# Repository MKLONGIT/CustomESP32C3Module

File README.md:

# CustomESP32C3Module
This is a barebones KiCAD project featuring a fully custom built ESP32 C3 board, alongside a DIY PCB antenna made with matlab.

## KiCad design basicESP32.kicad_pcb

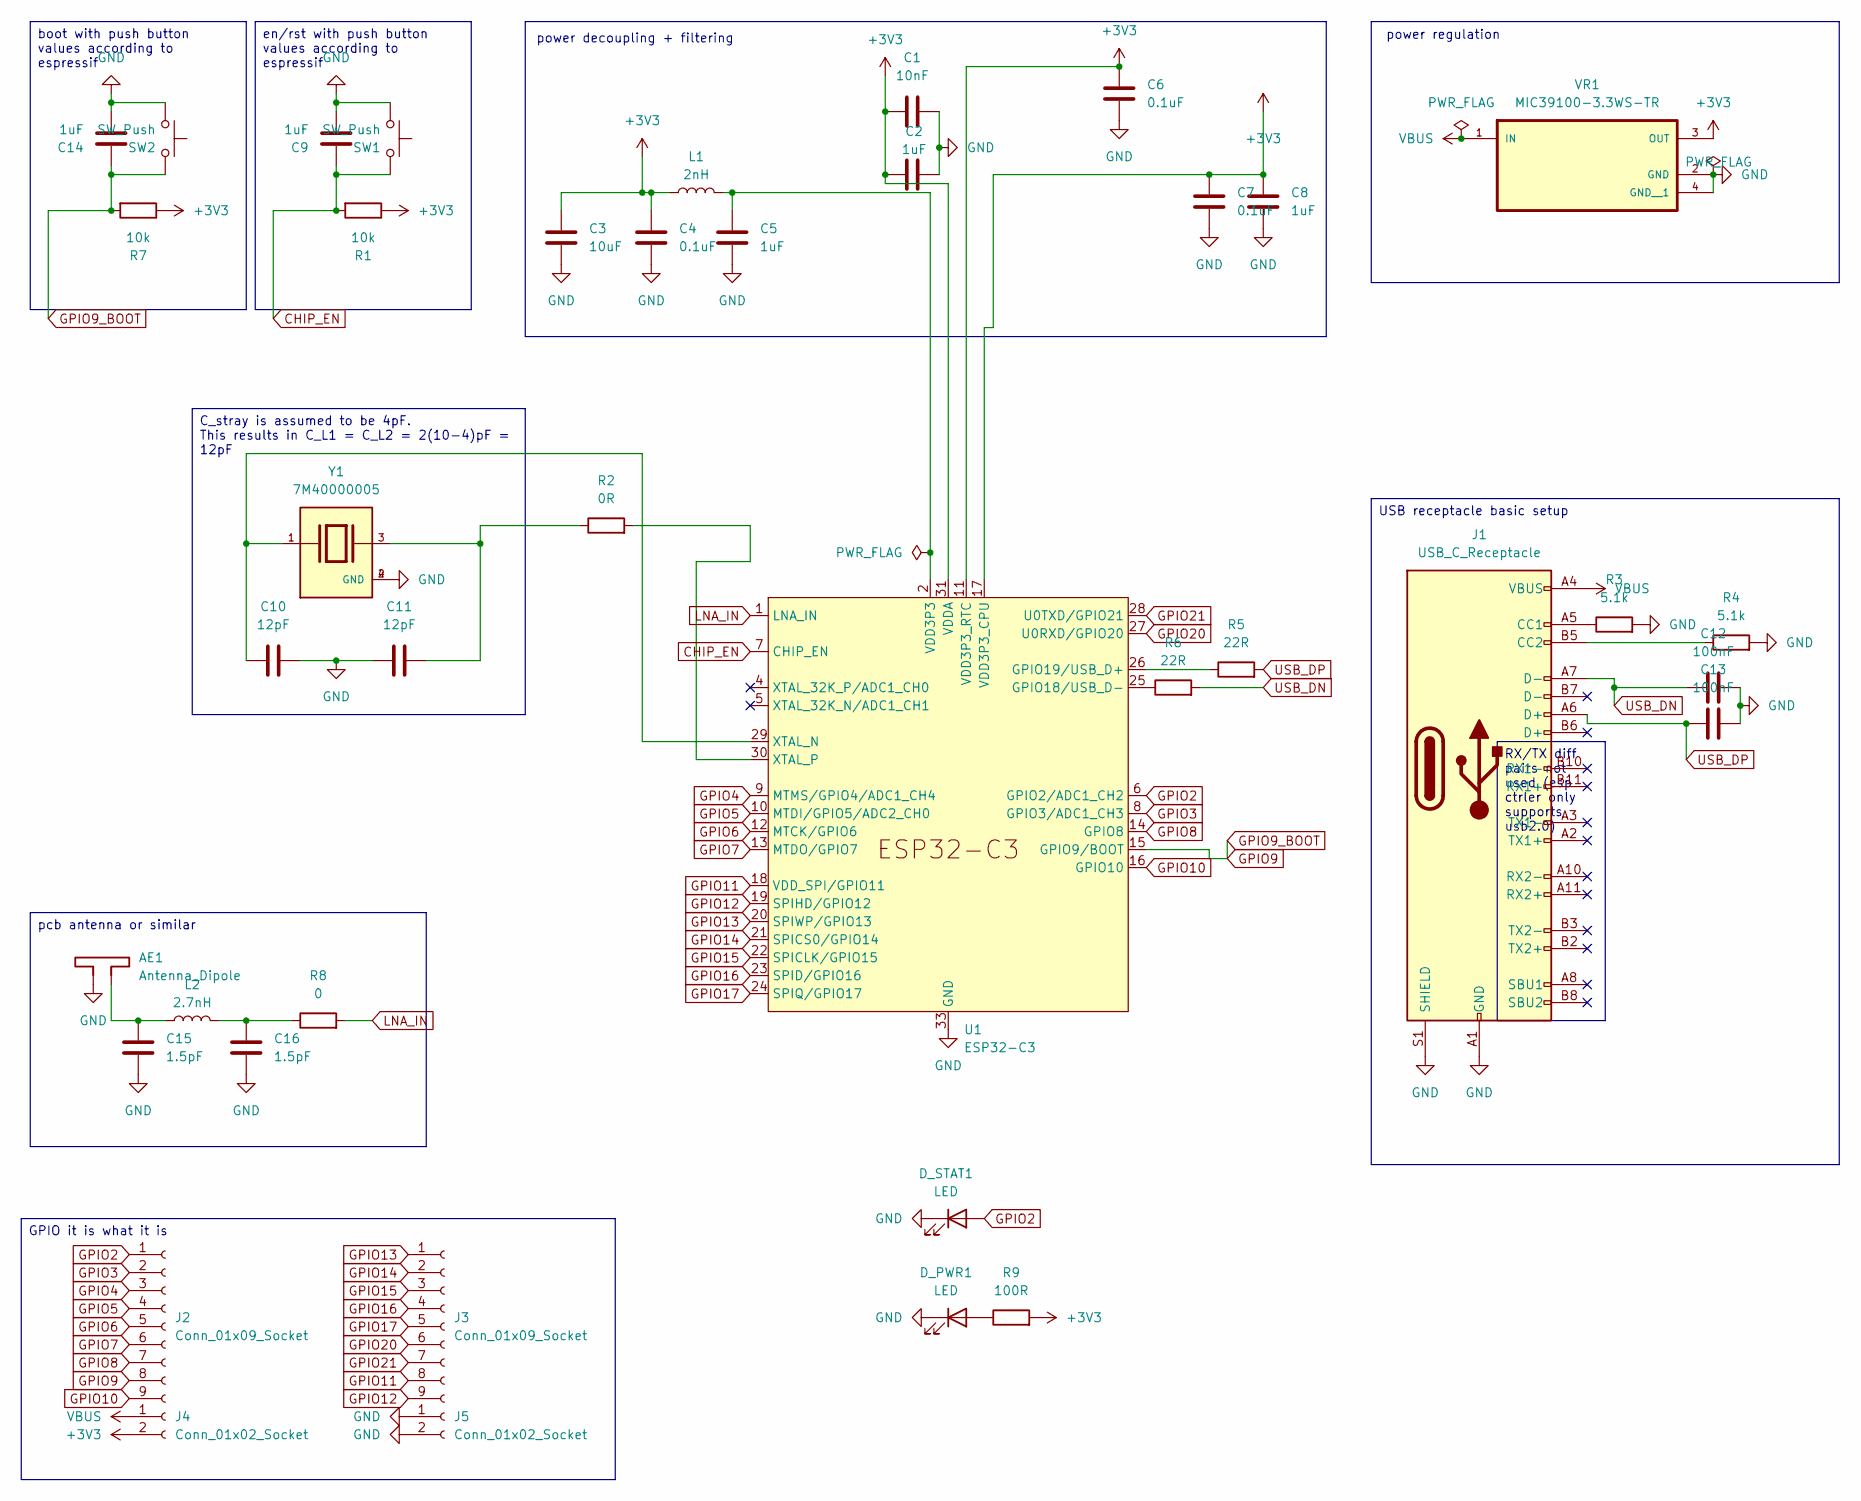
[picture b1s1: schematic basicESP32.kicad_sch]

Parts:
AE1: Antenna_Dipole; TODO
C1: 10nF; C_0603_1608Metric_Pad1.08x0.95mm_HandSolder
C2, C5, C8, C9, C14: 1uF; C_1206_3216Metric_Pad1.33x1.80mm_HandSolder
C3: 10uF; C_1206_3216Metric_Pad1.33x1.80mm_HandSolder
C4, C6, C7: 0.1uF; C_0603_1608Metric_Pad1.08x0.95mm_HandSolder
C10, C11: 12pF; C_0603_1608Metric_Pad1.08x0.95mm_HandSolder
C12, C13: 100nF; C_0603_1608Metric_Pad1.08x0.95mm_HandSolder
C15, C16: 1.5pF; C_0603_1608Metric_Pad1.08x0.95mm_HandSolder
D_PWR1: LED; LED_0603_1608Metric
D_STAT1: LED; LED_0603_1608Metric
J1: USB_C_Receptacle; USB_C_Receptacle_GCT_USB4085
J2, J3: Conn_01x09_Socket; TerminalBlock_Xinya_XY308-2.54-9P_1x09_P2.54mm_Horizontal
J4, J5: Conn_01x02_Socket; TerminalBlock_Xinya_XY308-2.54-2P_1x02_P2.54mm_Horizontal
L1: 2nH; L_0201_0603Metric_Pad0.64x0.40mm_HandSolder
L2: 2.7nH; L_0603_1608Metric
R1, R7: 10k; R_1206_3216Metric_Pad1.30x1.75mm_HandSolder
R2: 0R; TODO
R3, R4: 5.1k; R_1206_3216Metric_Pad1.30x1.75mm_HandSolder
R5, R6: 22R; R_1206_3216Metric_Pad1.30x1.75mm_HandSolder
R8: 0; R_0201_0603Metric
R9: 100R
SW1, SW2: SW_Push; SW_PUSH_6mm_H4.3mm
U1: ESP32-C3; QFN-32-1EP_5x5mm_P0.5mm_EP3.45x3.45mm
VR1: MIC39100-3.3WS-TR; SOT230P700X180-4N_MIC39100; PARTREV A
Y1: 7M40000005; XTAL_7M40000005; PARTREV N/A

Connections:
+3V3: C1.1, C2.1, C3.1, C4.1, C6.1, C7.1, C8.1, J4.2, L1.1, R1.1, R7.1, R9.2, U1.11 (VDD3P3_RTC), U1.17 (VDD3P3_CPU), U1.31 (VDDA), U1.32 (VDDA), VR1.3 (OUT)
CHIP_EN: C9.1, R1.2, SW1.2, U1.7 (CHIP_EN)
GND: AE1.1, C1.2, C2.2, C3.2, C4.2, C5.2, C6.2, C7.2, C8.2, C9.2, C10.2, C11.1, C12.2, C13.2, C14.2, C15.2, C16.2, D_PWR1.1 (K), D_STAT1.1 (K), J1.A1 (GND), J1.A12 (GND), J1.B1 (GND), J1.B12 (GND), J1.S1 (SHIELD), J5.1, J5.2, R3.2, R4.2, SW1.1, SW2.1, U1.33 (GND), VR1.2 (GND), VR1.4 (GND__1), Y1.2 (GND), Y1.4 (GND)
GPIO2: D_STAT1.2 (A), J2.1, U1.6 (GPIO2/ADC1_CH2)
GPIO3: J2.2, U1.8 (GPIO3/ADC1_CH3)
GPIO4: J2.3, U1.9 (MTMS/GPIO4/ADC1_CH4)
GPIO5: J2.4, U1.10 (MTDI/GPIO5/ADC2_CH0)
GPIO6: J2.5, U1.12 (MTCK/GPIO6)
GPIO7: J2.6, U1.13 (MTDO/GPIO7)
GPIO8: J2.7, U1.14 (GPIO8)
GPIO9: C14.1, J2.8, R7.2, SW2.2, U1.15 (GPIO9/BOOT)
GPIO10: J2.9, U1.16 (GPIO10)
GPIO11: J3.8, U1.18 (VDD_SPI/GPIO11)
GPIO12: J3.9, U1.19 (SPIHD/GPIO12)
GPIO13: J3.1, U1.20 (SPIWP/GPIO13)
GPIO14: J3.2, U1.21 (SPICS0/GPIO14)
GPIO15: J3.3, U1.22 (SPICLK/GPIO15)
GPIO16: J3.4, U1.23 (SPID/GPIO16)
GPIO17: J3.5, U1.24 (SPIQ/GPIO17)
GPIO20: J3.6, U1.27 (U0RXD/GPIO20)
GPIO21: J3.7, U1.28 (U0TXD/GPIO21)
LNA_IN: R8.2, U1.1 (LNA_IN)
unnamed: AE1.2, C15.1, L2.1
unnamed: C5.1, L1.2, U1.2 (VDD3P3), U1.3 (VDD3P3)
unnamed: C11.2, R2.1, Y1.3
unnamed: C16.1, L2.2, R8.1
unnamed: D_PWR1.2 (A), R9.1
unnamed: J1.A5 (CC1), R3.1
unnamed: J1.B5 (CC2), R4.1
unnamed: R6.1, U1.25 (GPIO18/USB_D-)
unnamed: R5.1, U1.26 (GPIO19/USB_D+)
unnamed: C10.1, U1.29 (XTAL_N), Y1.1
unnamed: R2.2, U1.30 (XTAL_P)
USB_DN: C12.1, J1.A7 (D-), R6.2
USB_DP: C13.1, J1.A6 (D+), R5.2
VBUS: J1.A4 (VBUS), J1.A9 (VBUS), J1.B4 (VBUS), J1.B9 (VBUS), J4.1, VR1.1 (IN)

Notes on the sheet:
power regulation
power decoupling + filtering
USB receptacle basic setup
pcb antenna or similar
boot with push button values according to espressif
GPIO it is what it is
en/rst with push button values according to espressif
RX/TX diff pairs not used (esp ctrler only supports usb2.0)
C_stray is assumed to be 4pF. This results in C_L1 = C_L2 = 2(10-4)pF = 12pF

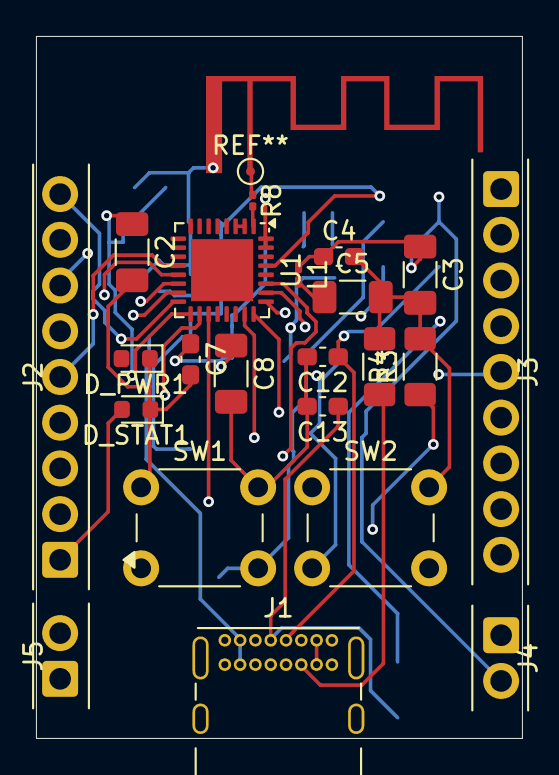
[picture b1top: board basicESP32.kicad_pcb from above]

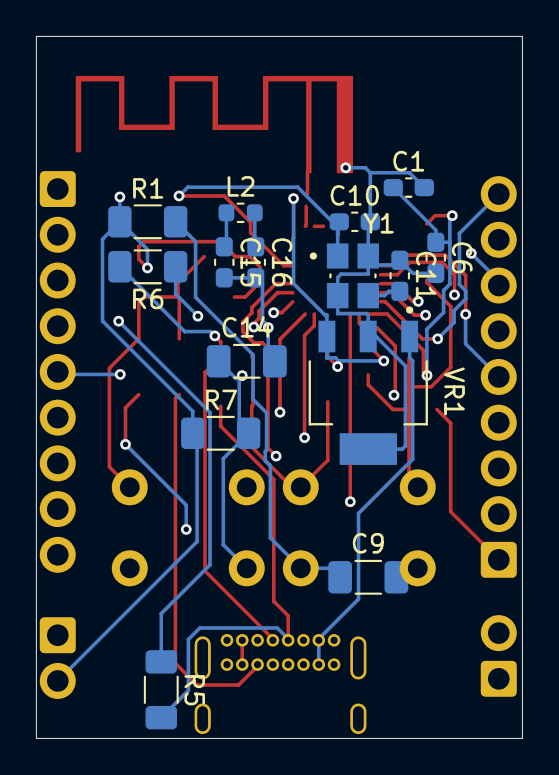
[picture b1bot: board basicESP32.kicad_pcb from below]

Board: 4 copper layers, 27.0 x 39.0 mm, 37 parts (15 on the bottom side), 34 nets.

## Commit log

2025-03-21 Initial commit: First iteration of the custom module.
2025-03-21 Initial commit: first iteration of custom pcb
